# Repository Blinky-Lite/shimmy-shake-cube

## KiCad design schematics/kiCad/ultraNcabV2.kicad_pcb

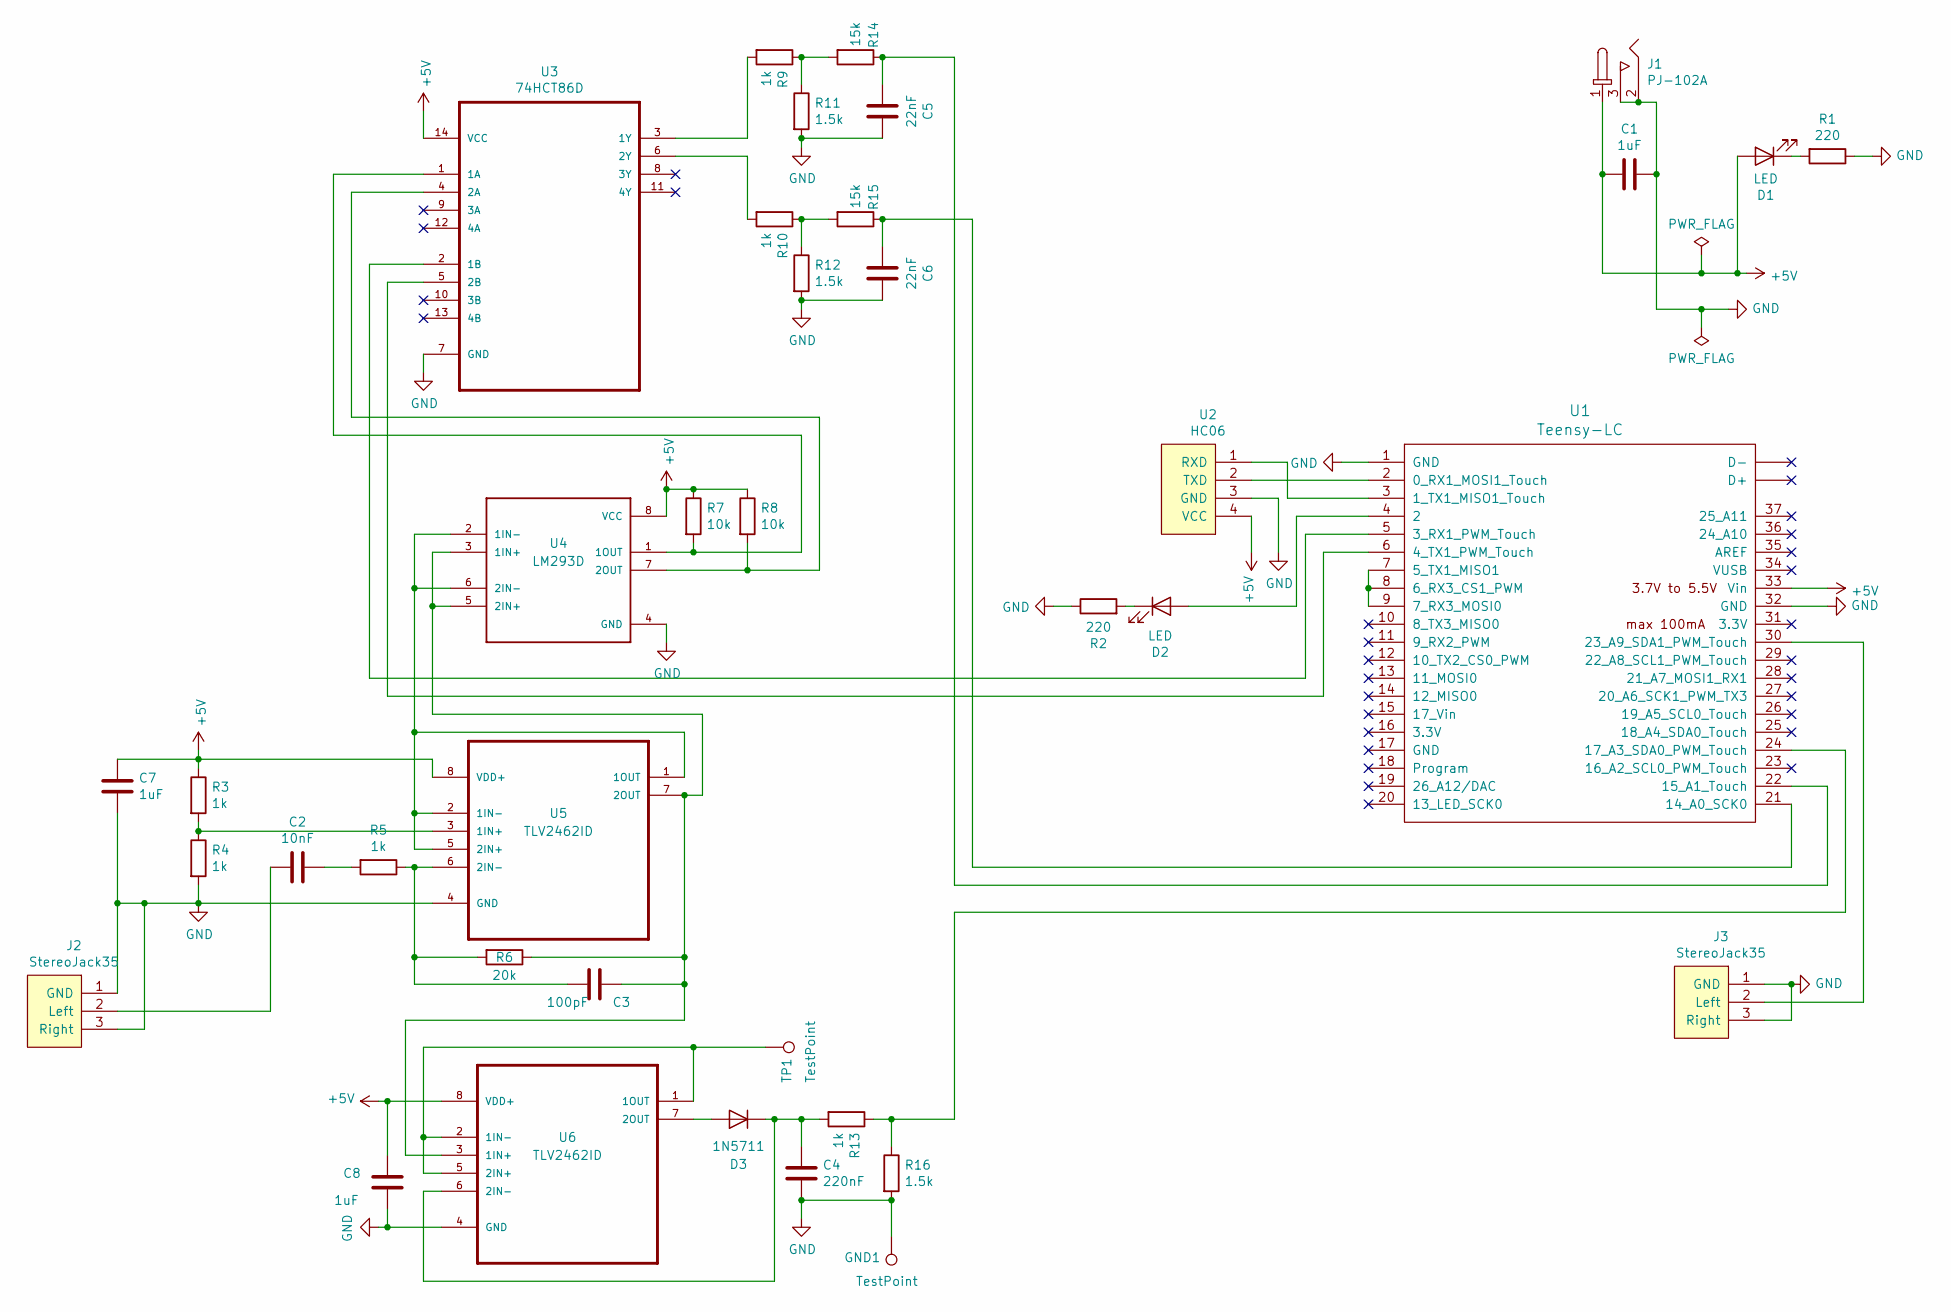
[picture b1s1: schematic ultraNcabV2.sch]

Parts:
C1, C7, C8: 1uF; C_1206_3216Metric_Pad1.42x1.75mm_HandSolder
C2: 10nF; C_1206_3216Metric_Pad1.42x1.75mm_HandSolder
C3: 100pF; C_1206_3216Metric_Pad1.42x1.75mm_HandSolder
C4: 220nF; C_1206_3216Metric_Pad1.42x1.75mm_HandSolder
C5, C6: 22nF; C_1206_3216Metric_Pad1.42x1.75mm_HandSolder
D1, D2: LED; LED_D5.0mm
D3: 1N5711; D_DO-35_SOD27_P7.62mm_Horizontal
GND1: TestPoint; TestPoint_THTPad_2.0x2.0mm_Drill1.0mm
J1: PJ-102A; DC21Jack
J2, J3: StereoJack35
R1, R2: 220; R_1206_3216Metric_Pad1.42x1.75mm_HandSolder
R3, R4, R5, R9, R10, R13: 1k; R_1206_3216Metric_Pad1.42x1.75mm_HandSolder
R6: 20k; R_1206_3216Metric_Pad1.42x1.75mm_HandSolder
R7, R8: 10k; R_1206_3216Metric_Pad1.42x1.75mm_HandSolder
R11, R12, R16: 1.5k; R_1206_3216Metric_Pad1.42x1.75mm_HandSolder
R14, R15: 15k; R_1206_3216Metric_Pad1.42x1.75mm_HandSolder
TP1: TestPoint; TestPoint_THTPad_2.0x2.0mm_Drill1.0mm
U1: Teensy-LC; Teensy30_31_32_LC
U2: HC06
U3: 74HCT86D; SOIC127P600X175-14N
U4: LM293D; SOIC127P600X175-8N
U5, U6: TLV2462ID; SOIC127P600X175-8N

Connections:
+5V: C1.2, C7.1, C8.1, D1.2 (A), J1.1, R3.1, R7.1, R8.1, U1.33 (Vin), U2.4 (VCC), U3.14 (VCC), U4.8 (VCC), U5.8 (VDD+), U6.8 (VDD+)
GND: C1.1, C4.2, C5.2, C6.2, C7.2, C8.2, GND1.1, J1.2, J1.3, J2.1 (GND), J2.3 (Right), J3.1 (GND), J3.3 (Right), R1.1, R2.1, R4.2, R11.2, R12.2, R16.2, U1.1 (GND), U1.32 (GND), U2.3 (GND), U3.7 (GND), U4.4 (GND), U5.4 (GND), U6.4 (GND)
unnamed: C2.1, J2.2 (Left)
unnamed: C2.2, R5.2
unnamed: C3.1, R5.1, R6.2, U5.6 (2IN-)
unnamed: C3.2, R6.1, U4.3 (1IN+), U4.5 (2IN+), U5.7 (2OUT), U6.3 (1IN+)
unnamed: C4.1, D3.1 (K), R13.2, U6.6 (2IN-)
unnamed: C5.1, R14.1, U1.22 (15_A1_Touch)
unnamed: C6.1, R15.1, U1.21 (14_A0_SCK0)
unnamed: D1.1 (K), R1.2
unnamed: D2.1 (K), R2.2
unnamed: D2.2 (A), U1.4 (2)
unnamed: D3.2 (A), U6.7 (2OUT)
unnamed: J3.2 (Left), U1.30 (23_A9_SDA1_PWM_Touch)
unnamed: R3.2, R4.1, U5.3 (1IN+)
unnamed: R7.2, U3.1 (1A), U4.1 (1OUT)
unnamed: R8.2, U3.4 (2A), U4.7 (2OUT)
unnamed: R9.2, U3.3 (1Y)
unnamed: R10.1, R12.1, R15.2
unnamed: R10.2, U3.6 (2Y)
unnamed: R9.1, R11.1, R14.2
unnamed: R13.1, R16.1, U1.24 (17_A3_SDA0_PWM_Touch)
unnamed: TP1.1, U6.1 (1OUT), U6.2 (1IN-), U6.5 (2IN+)
unnamed: U1.2 (0_RX1_MOSI1_Touch), U2.2 (TXD)
unnamed: U1.3 (1_TX1_MISO1_Touch), U2.1 (RXD)
unnamed: U1.5 (3_RX1_PWM_Touch), U3.2 (1B)
unnamed: U1.6 (4_TX1_PWM_Touch), U3.5 (2B)
unnamed: U1.7 (5_TX1_MISO1), U1.8 (6_RX3_CS1_PWM), U1.9 (7_RX3_MOSI0)
unnamed: U4.2 (1IN-), U4.6 (2IN-), U5.1 (1OUT), U5.2 (1IN-), U5.5 (2IN+)

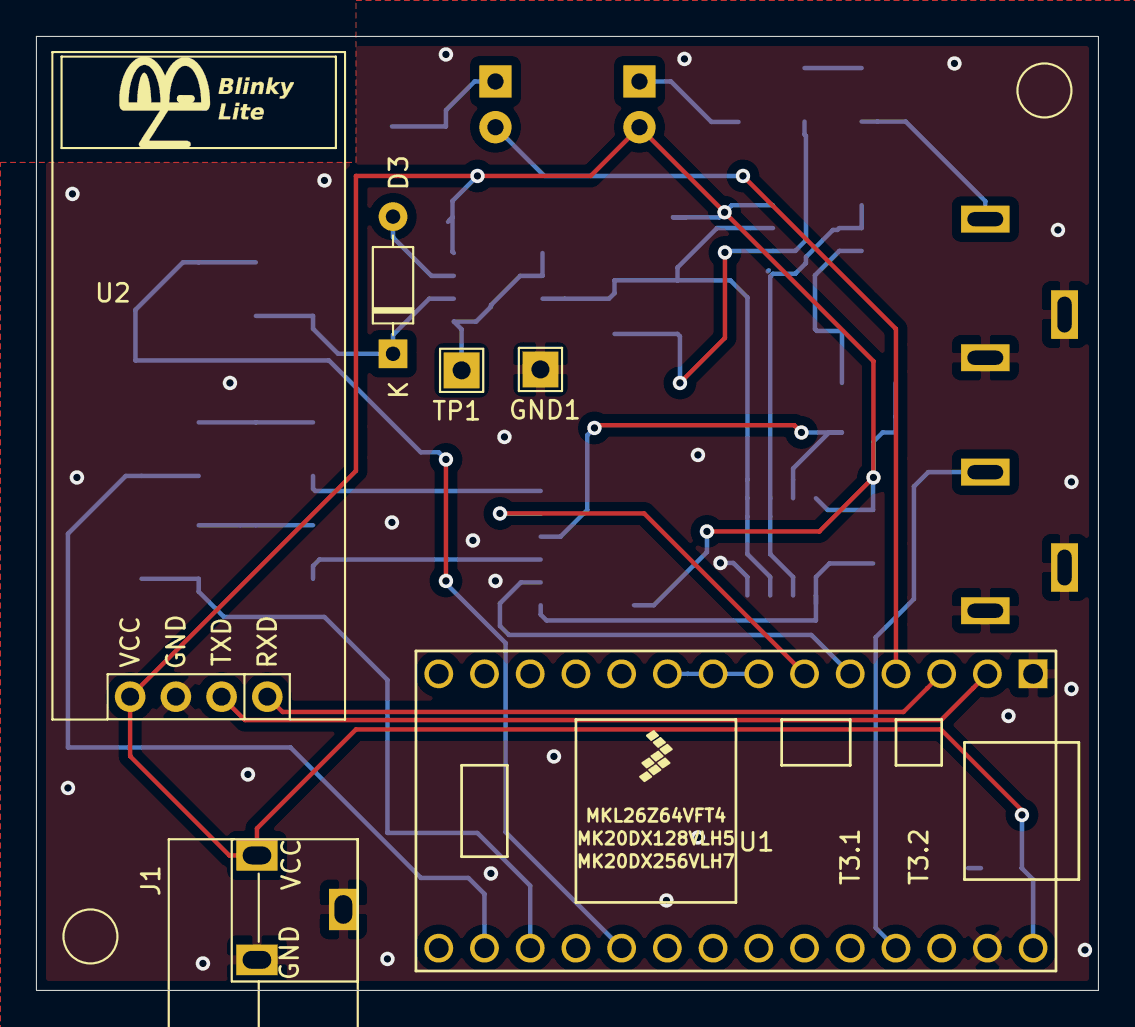
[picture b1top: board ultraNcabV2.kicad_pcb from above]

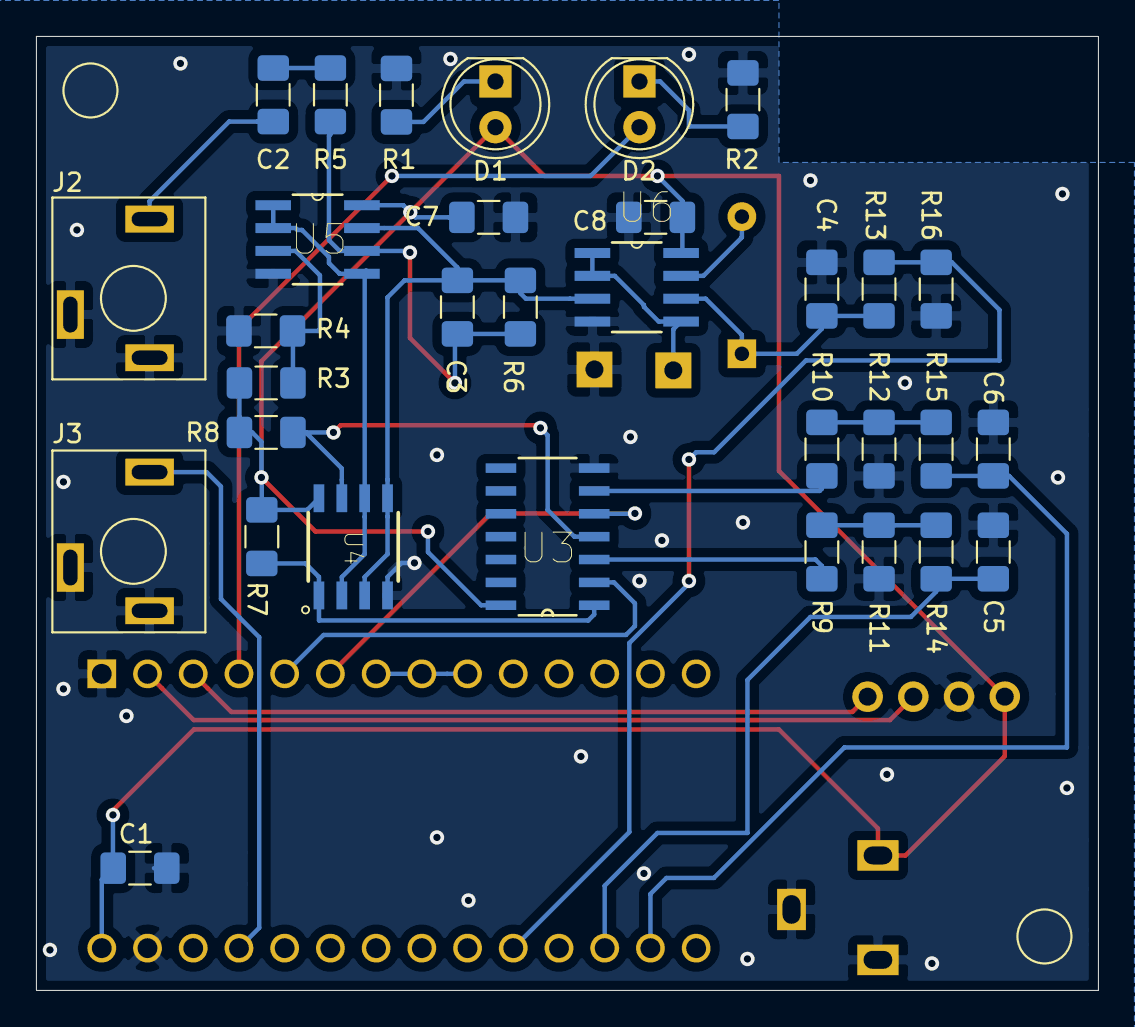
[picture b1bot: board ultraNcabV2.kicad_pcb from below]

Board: 2 copper layers, 59.0 x 53.0 mm, 38 parts (32 on the bottom side), 29 nets.

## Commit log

2020-02-27 added kicad schem
2020-02-27 removed fritzing
2020-02-27 worked on init scenarios
2020-03-01 slimmed down serial comm
2020-03-04 update on hc06
2020-04-06 master driven code
2021-02-11 test code using interval timers
